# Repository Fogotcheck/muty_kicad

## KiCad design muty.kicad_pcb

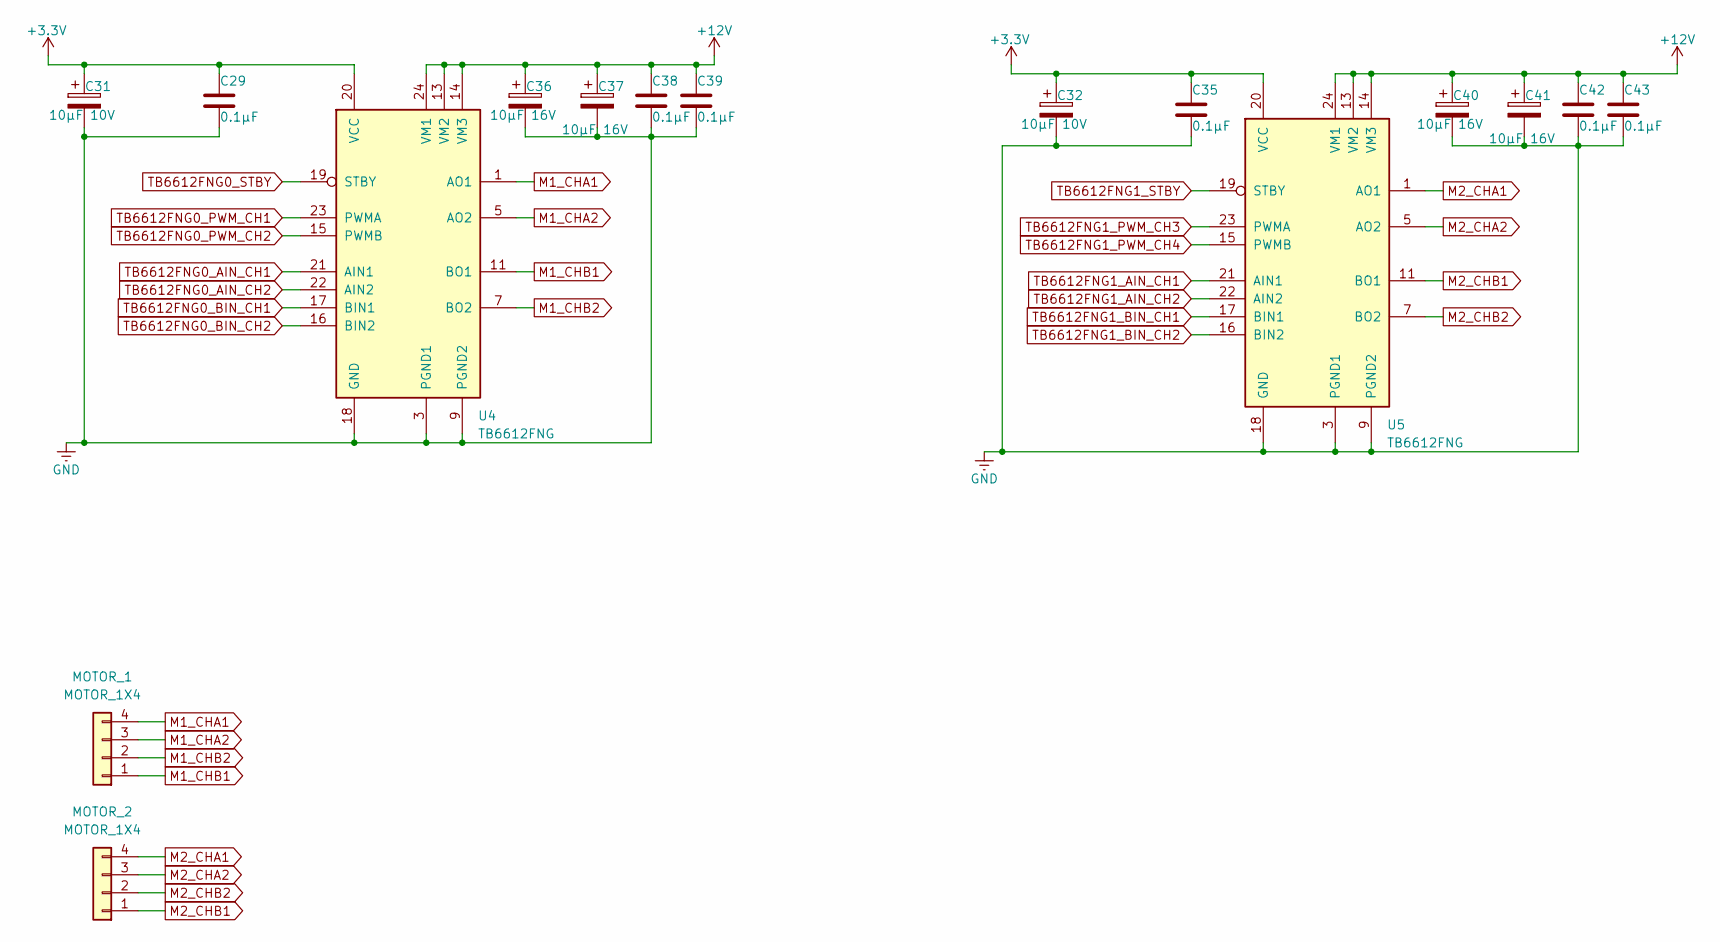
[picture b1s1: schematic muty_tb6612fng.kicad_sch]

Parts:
C29, C35, C38, C39, C42, C43: 0.1μF; C_0603_1608Metric_Pad1.08x0.95mm_HandSolder
C31, C32: 10μF 10V; CP_EIA-1608-10_AVX-L_HandSolder
C36, C37, C40, C41: 10μF 16V; CP_EIA-3528-15_AVX-H_HandSolder
MOTOR_1, MOTOR_2: MOTOR_1X4; JST_EH_S4B-EH_1x04_P2.50mm_Horizontal
U4, U5: TB6612FNG; SSOP-24_5.3x8.2mm_P0.65mm

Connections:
+3.3V: C29.2, C31.1, C32.1, C35.2, U4.20 (VCC), U5.20 (VCC); also elsewhere on the board
+12V: C36.1, C37.1, C38.2, C39.2, C40.1, C41.1, C42.2, C43.2, U4.13 (VM2), U4.14 (VM3), U4.24 (VM1), U5.13 (VM2), U5.14 (VM3), U5.24 (VM1); also elsewhere on the board
GND: C29.1, C31.2, C32.2, C35.1, C36.2, C37.2, C38.1, C39.1, C40.2, C41.2, C42.1, C43.1, U4.3 (PGND1), U4.4 (PGND1), U4.9 (PGND2), U4.10 (PGND2), U4.18 (GND), U5.3 (PGND1), U5.4 (PGND1), U5.9 (PGND2), U5.10 (PGND2), U5.18 (GND); also elsewhere on the board
M1_CHA1: MOTOR_1.4, U4.1 (AO1), U4.2 (AO1)
M1_CHA2: MOTOR_1.3, U4.5 (AO2), U4.6 (AO2)
M1_CHB1: MOTOR_1.1, U4.11 (BO1), U4.12 (BO1)
M1_CHB2: MOTOR_1.2, U4.7 (BO2), U4.8 (BO2)
M2_CHA1: MOTOR_2.4, U5.1 (AO1), U5.2 (AO1)
M2_CHA2: MOTOR_2.3, U5.5 (AO2), U5.6 (AO2)
M2_CHB1: MOTOR_2.1, U5.11 (BO1), U5.12 (BO1)
M2_CHB2: MOTOR_2.2, U5.7 (BO2), U5.8 (BO2)
TB6612FNG0_AIN_CH1: U4.21 (AIN1); also elsewhere on the board
TB6612FNG0_AIN_CH2: U4.22 (AIN2); also elsewhere on the board
TB6612FNG0_BIN_CH1: U4.17 (BIN1); also elsewhere on the board
TB6612FNG0_BIN_CH2: U4.16 (BIN2); also elsewhere on the board
TB6612FNG0_PWM_CH1: U4.23 (PWMA); also elsewhere on the board
TB6612FNG0_PWM_CH2: U4.15 (PWMB); also elsewhere on the board
TB6612FNG0_STBY: U4.19 (STBY); also elsewhere on the board
TB6612FNG1_AIN_CH1: U5.21 (AIN1); also elsewhere on the board
TB6612FNG1_AIN_CH2: U5.22 (AIN2); also elsewhere on the board
TB6612FNG1_BIN_CH1: U5.17 (BIN1); also elsewhere on the board
TB6612FNG1_BIN_CH2: U5.16 (BIN2); also elsewhere on the board
TB6612FNG1_PWM_CH3: U5.23 (PWMA); also elsewhere on the board
TB6612FNG1_PWM_CH4: U5.15 (PWMB); also elsewhere on the board
TB6612FNG1_STBY: U5.19 (STBY); also elsewhere on the board

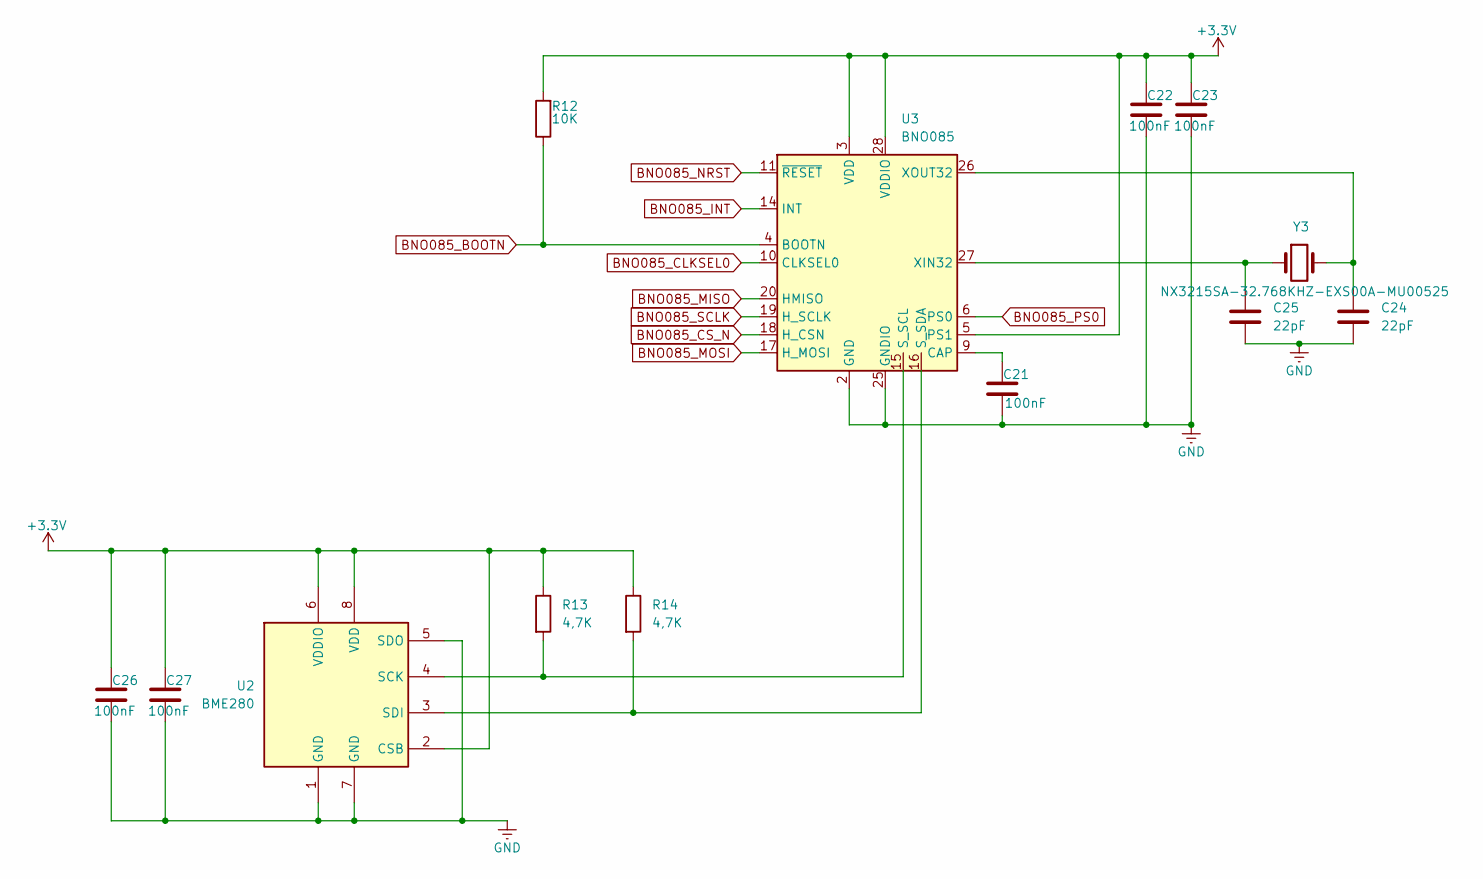
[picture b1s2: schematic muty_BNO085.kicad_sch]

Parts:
C21, C22, C23, C26, C27: 100nF; C_0603_1608Metric_Pad1.08x0.95mm_HandSolder
C24, C25: 22pF; C_0805_2012Metric_Pad1.18x1.45mm_HandSolder
R12: 10K; R_0805_2012Metric_Pad1.20x1.40mm_HandSolder
R13, R14: 4,7K; R_0805_2012Metric_Pad1.20x1.40mm_HandSolder
U2: BME280; Bosch_LGA-8_2.5x2.5mm_P0.65mm_ClockwisePinNumbering
U3: BNO085; LGA-28_5.2x3.8mm_P0.5mm
Y3: NX3215SA-32.768KHZ-EXS00A-MU00525; Crystal_SMD_3215-2Pin_3.2x1.5mm

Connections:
+3.3V: C22.2, C23.2, C26.2, C27.2, R12.2, R13.1, R14.1, U2.2 (CSB), U2.6 (VDDIO), U2.8 (VDD), U3.3 (VDD), U3.5 (PS1), U3.28 (VDDIO); also elsewhere on the board
BNO085_BOOTN: R12.1, U3.4 (BOOTN); also elsewhere on the board
BNO085_CLKSEL0: U3.10 (CLKSEL0); also elsewhere on the board
BNO085_CS_N: U3.18 (H_CSN); also elsewhere on the board
BNO085_INT: U3.14 (INT); also elsewhere on the board
BNO085_MISO: U3.20 (HMISO); also elsewhere on the board
BNO085_MOSI: U3.17 (H_MOSI); also elsewhere on the board
BNO085_NRST: U3.11 (~RESET); also elsewhere on the board
BNO085_PS0: U3.6 (PS0); also elsewhere on the board
BNO085_SCLK: U3.19 (H_SCLK); also elsewhere on the board
GND: C21.1, C22.1, C23.1, C24.1, C25.1, C26.1, C27.1, U2.1 (GND), U2.5 (SDO), U2.7 (GND), U3.2 (GND), U3.25 (GNDIO); also elsewhere on the board
unnamed: R13.2, U2.4 (SCK), U3.15 (S_SCL)
unnamed: R14.2, U2.3 (SDI), U3.16 (S_SDA)
unnamed: C21.2, U3.9 (CAP)
unnamed: C25.2, U3.27 (XIN32), Y3.1
unnamed: C24.2, U3.26 (XOUT32), Y3.2

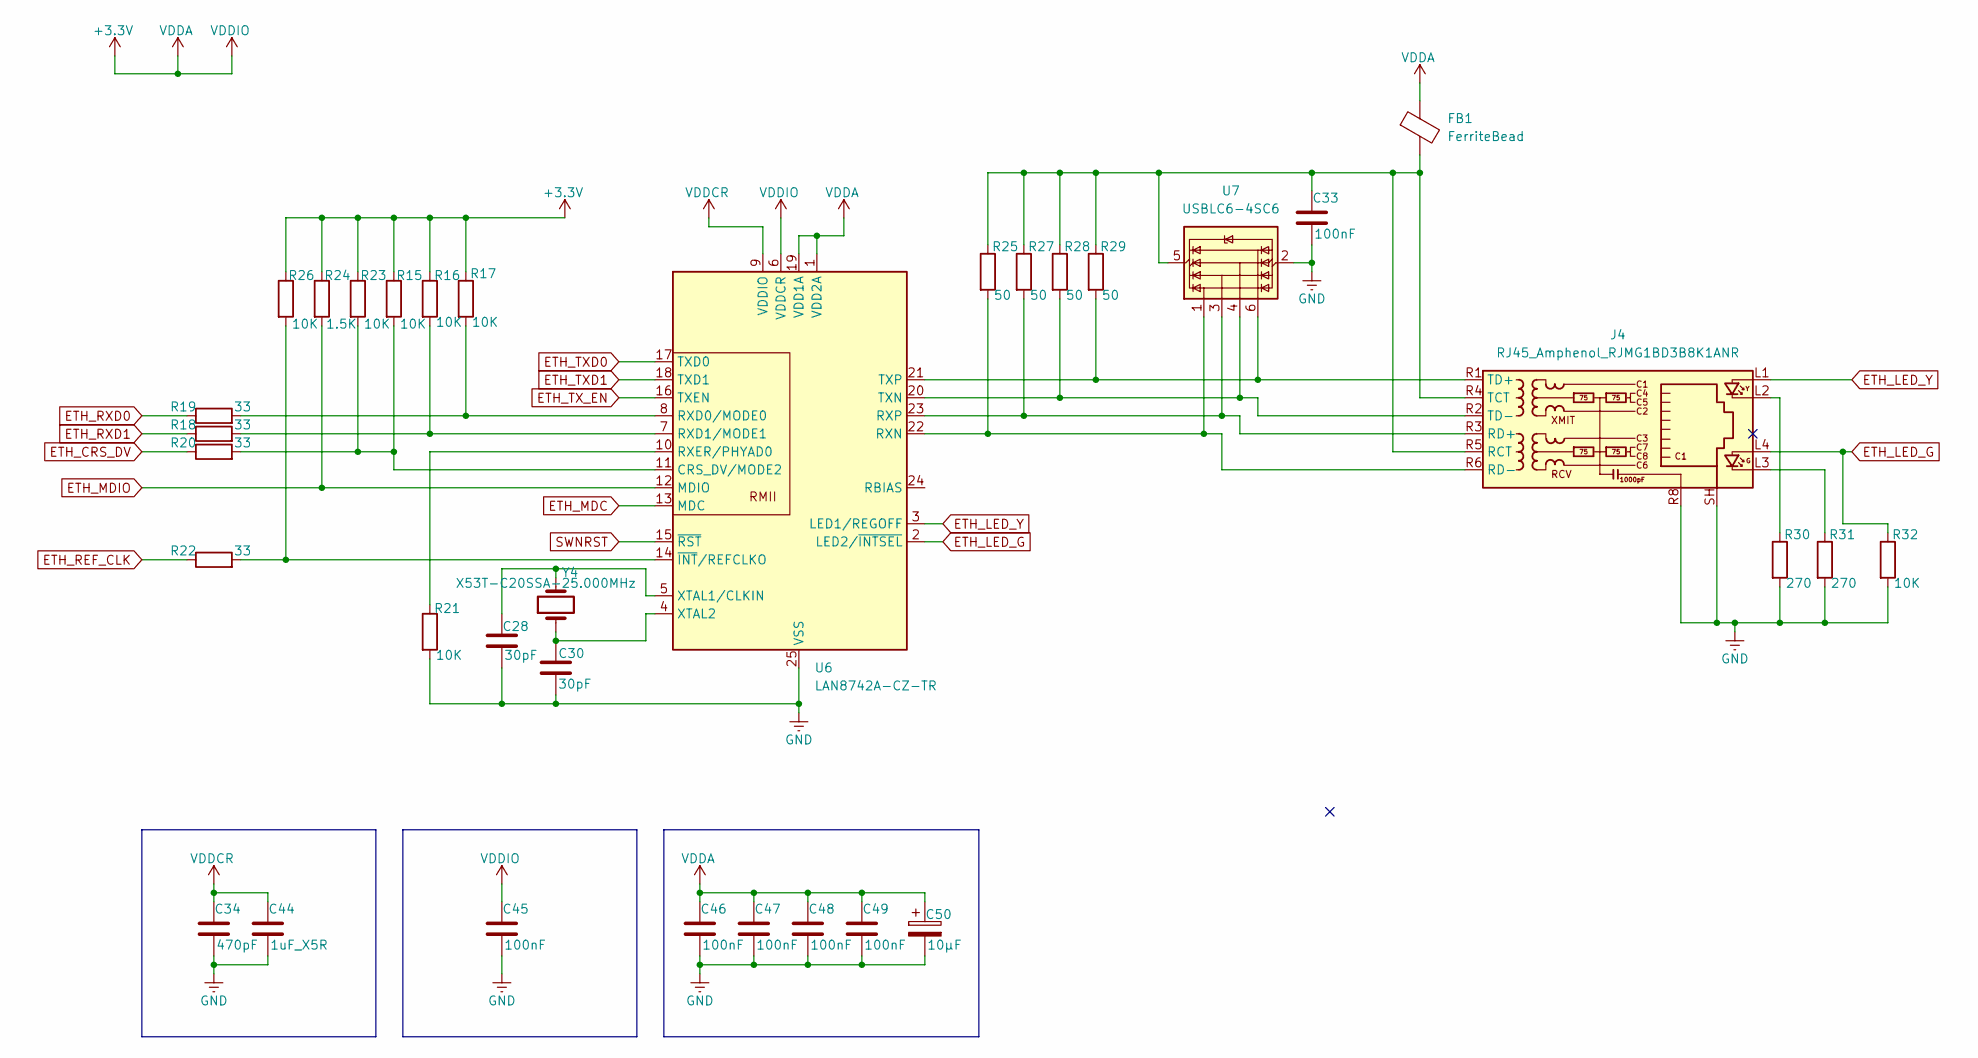
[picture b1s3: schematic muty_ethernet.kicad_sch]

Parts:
C28, C30: 30pF; C_0805_2012Metric_Pad1.18x1.45mm_HandSolder
C33, C45, C46, C47, C48, C49: 100nF; C_0603_1608Metric_Pad1.08x0.95mm_HandSolder
C34: 470pF; C_0603_1608Metric_Pad1.08x0.95mm_HandSolder
C44: 1uF_X5R; C_0603_1608Metric_Pad1.08x0.95mm_HandSolder
C50: 10μF; CP_EIA-1608-10_AVX-L_HandSolder
FB1: FerriteBead; L_0805_2012Metric_Pad1.05x1.20mm_HandSolder
J4: RJ45_Amphenol_RJMG1BD3B8K1ANR
R15, R16, R17, R21, R23, R26, R32: 10K; R_0805_2012Metric_Pad1.20x1.40mm_HandSolder
R18, R19, R20, R22: 33; R_0805_2012Metric_Pad1.20x1.40mm_HandSolder
R24: 1.5K; R_0805_2012Metric_Pad1.20x1.40mm_HandSolder
R25, R27, R28, R29: 50; R_0805_2012Metric_Pad1.20x1.40mm_HandSolder
R30, R31: 270; R_0805_2012Metric_Pad1.20x1.40mm_HandSolder
U6: LAN8742A-CZ-TR; VQFN-24-1EP_4x4mm_P0.5mm_EP2.5x2.5mm_ThermalVias
U7: USBLC6-4SC6; SOT-23-6
Y4: X53T-C20SSA-25.000MHz; Crystal_SMD_5032-2Pin_5.0x3.2mm

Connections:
+3.3V: C45.2, C46.2, C47.2, C48.2, C49.2, C50.1, FB1.1, R15.1, R16.1, R17.1, R23.1, R24.1, R26.1, U6.1 (VDD2A), U6.6 (VDDCR), U6.19 (VDD1A); also elsewhere on the board
ETH_CRS_DV: R20.1; also elsewhere on the board
ETH_LED_G: J4.L4, R32.1, U6.2 (LED2/~INTSEL)
ETH_LED_Y: J4.L1, U6.3 (LED1/REGOFF)
ETH_MDC: U6.13 (MDC); also elsewhere on the board
ETH_MDIO: R24.2, U6.12 (MDIO); also elsewhere on the board
ETH_REF_CLK: R22.1; also elsewhere on the board
ETH_RXD0: R19.1; also elsewhere on the board
ETH_RXD1: R18.1; also elsewhere on the board
ETH_TXD0: U6.17 (TXD0); also elsewhere on the board
ETH_TXD1: U6.18 (TXD1); also elsewhere on the board
ETH_TX_EN: U6.16 (TXEN); also elsewhere on the board
GND: C28.1, C30.1, C33.1, C34.1, C44.1, C45.1, C46.1, C47.1, C48.1, C49.1, C50.2, J4.R8, J4.SH, R21.2, R30.2, R31.2, R32.2, U6.25 (VSS), U7.2 (GND); also elsewhere on the board
unnamed: J4.L2, R30.1
unnamed: J4.L3, R31.1
unnamed: C33.2, FB1.2, J4.R4 (TCT), J4.R5 (RCT), R25.1, R27.1, R28.1, R29.1, U7.5 (VBUS)
unnamed: J4.R3 (RD+), R27.2, U6.23 (RXP), U7.3 (I/O2)
unnamed: J4.R6 (RD-), R25.2, U6.22 (RXN), U7.1 (I/O1)
unnamed: J4.R1 (TD+), R29.2, U6.21 (TXP), U7.6 (I/O4)
unnamed: J4.R2 (TD-), R28.2, U6.20 (TXN), U7.4 (I/O3)
unnamed: R15.2, R20.2, R23.2, U6.11 (CRS_DV/MODE2)
unnamed: R17.2, R19.2, U6.8 (RXD0/MODE0)
unnamed: R16.2, R18.2, U6.7 (RXD1/MODE1)
unnamed: R21.1, U6.10 (RXER/PHYAD0)
unnamed: C28.2, U6.5 (XTAL1/CLKIN), Y4.2
unnamed: C30.2, U6.4 (XTAL2), Y4.1
unnamed: R22.2, R26.2, U6.14 (~INT/REFCLKO)
SWNRST: U6.15 (~RST); also elsewhere on the board
VDDCR: C34.2, C44.2, U6.9 (VDDIO)

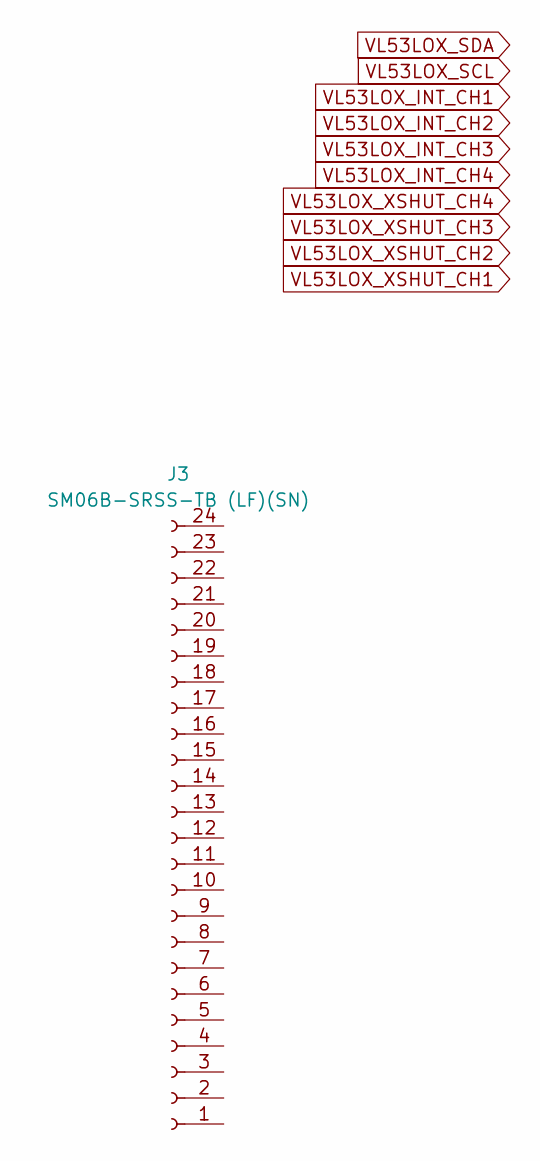
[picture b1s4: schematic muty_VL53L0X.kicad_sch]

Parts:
J3: SM06B-SRSS-TB (LF)(SN)

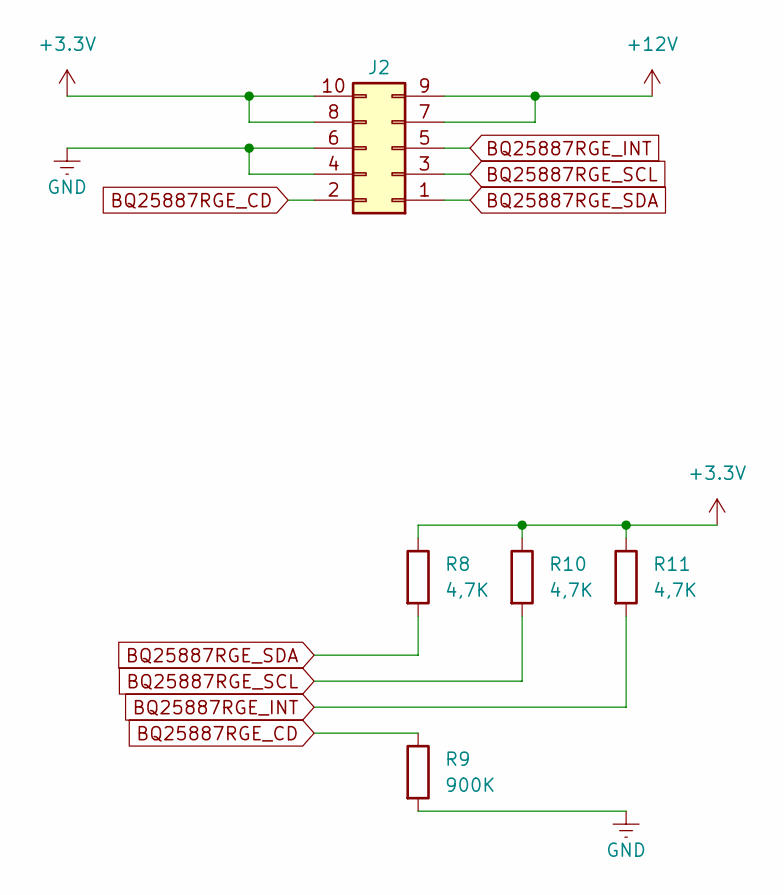
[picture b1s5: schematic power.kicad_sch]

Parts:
J2: Conn_02x05_Odd_Even; JST_PHD_B10B-PHDSS_2x05_P2.00mm_Vertical
R8, R10, R11: 4,7K; R_0805_2012Metric_Pad1.20x1.40mm_HandSolder
R9: 900K; R_0805_2012Metric_Pad1.20x1.40mm_HandSolder

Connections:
+3.3V: J2.8, J2.10, R8.1, R10.1, R11.1; also elsewhere on the board
+12V: J2.7, J2.9; also elsewhere on the board
BQ25887RGE_CD: J2.2, R9.1; also elsewhere on the board
BQ25887RGE_INT: J2.5, R11.2; also elsewhere on the board
BQ25887RGE_SCL: J2.3, R10.2; also elsewhere on the board
BQ25887RGE_SDA: J2.1, R8.2; also elsewhere on the board
GND: J2.4, J2.6, R9.2; also elsewhere on the board

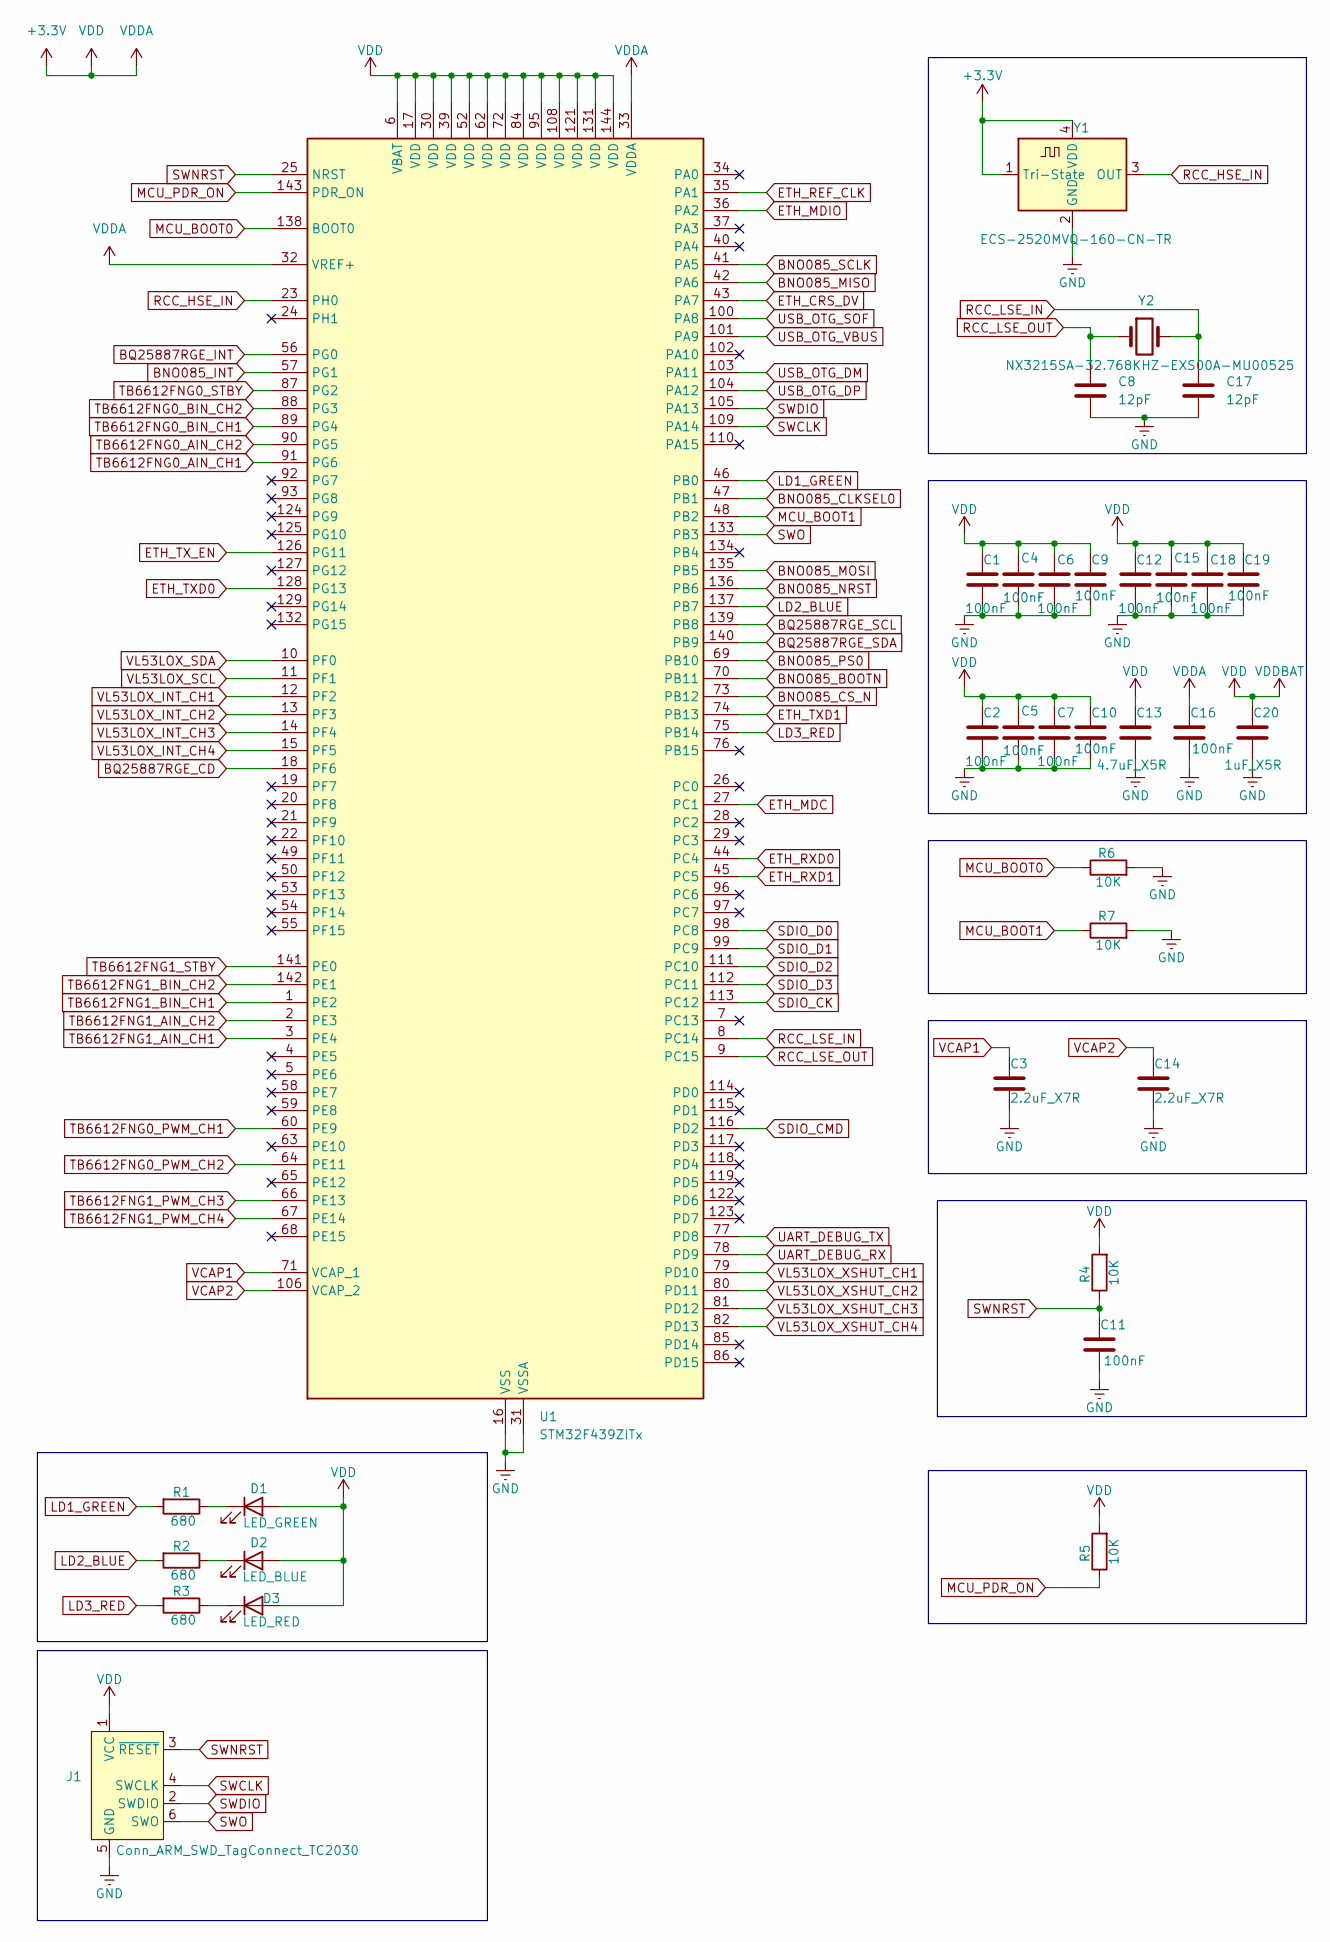
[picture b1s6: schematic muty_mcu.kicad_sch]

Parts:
C1, C2, C4, C5, C6, C7, C9, C10, C11, C12, C15, C16, C18, C19: 100nF; C_0603_1608Metric_Pad1.08x0.95mm_HandSolder
C3, C14: 2.2uF_X7R; C_0805_2012Metric_Pad1.18x1.45mm_HandSolder
C8, C17: 12pF; C_0805_2012Metric_Pad1.18x1.45mm_HandSolder
C13: 4.7uF_X5R; C_0603_1608Metric_Pad1.08x0.95mm_HandSolder
C20: 1uF_X5R; C_0603_1608Metric_Pad1.08x0.95mm_HandSolder
D1: LED_GREEN; LED_0603_1608Metric_Pad1.05x0.95mm_HandSolder
D2: LED_BLUE; LED_0603_1608Metric_Pad1.05x0.95mm_HandSolder
D3: LED_RED; LED_0603_1608Metric_Pad1.05x0.95mm_HandSolder
J1: Conn_ARM_SWD_TagConnect_TC2030; Tag-Connect_TC2030-IDC-FP_2x03_P1.27mm_Vertical
R1, R2, R3: 680; R_0805_2012Metric_Pad1.20x1.40mm_HandSolder
R4, R5, R6, R7: 10K; R_0805_2012Metric_Pad1.20x1.40mm_HandSolder
U1: STM32F439ZITx; LQFP-144_20x20mm_P0.5mm
Y1: ECS-2520MVQ-160-CN-TR; Oscillator_SMD_ECS_2520MV-xxx-xx-4Pin_2.5x2.0mm
Y2: NX3215SA-32.768KHZ-EXS00A-MU00525; Crystal_SMD_3215-2Pin_3.2x1.5mm

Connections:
+3.3V: C1.2, C2.2, C4.2, C5.2, C6.2, C7.2, C9.2, C10.2, C12.2, C13.2, C15.2, C16.2, C18.2, C19.2, C20.2, D1.2 (A), D2.2 (A), D3.2 (A), J1.1 (VCC), R4.2, R5.2, U1.6 (VBAT), U1.17 (VDD), U1.30 (VDD), U1.32 (VREF+), U1.33 (VDDA), U1.39 (VDD), U1.52 (VDD), U1.62 (VDD), U1.72 (VDD), U1.84 (VDD), U1.95 (VDD), U1.108 (VDD), U1.121 (VDD), U1.131 (VDD), U1.144 (VDD), Y1.1 (Tri-State), Y1.4 (VDD); also elsewhere on the board
BNO085_BOOTN: U1.70 (PB11); also elsewhere on the board
BNO085_CLKSEL0: U1.47 (PB1); also elsewhere on the board
BNO085_CS_N: U1.73 (PB12); also elsewhere on the board
BNO085_INT: U1.57 (PG1); also elsewhere on the board
BNO085_MISO: U1.42 (PA6); also elsewhere on the board
BNO085_MOSI: U1.135 (PB5); also elsewhere on the board
BNO085_NRST: U1.136 (PB6); also elsewhere on the board
BNO085_PS0: U1.69 (PB10); also elsewhere on the board
BNO085_SCLK: U1.41 (PA5); also elsewhere on the board
BQ25887RGE_CD: U1.18 (PF6); also elsewhere on the board
BQ25887RGE_INT: U1.56 (PG0); also elsewhere on the board
BQ25887RGE_SCL: U1.139 (PB8); also elsewhere on the board
BQ25887RGE_SDA: U1.140 (PB9); also elsewhere on the board
ETH_CRS_DV: U1.43 (PA7); also elsewhere on the board
ETH_MDC: U1.27 (PC1); also elsewhere on the board
ETH_MDIO: U1.36 (PA2); also elsewhere on the board
ETH_REF_CLK: U1.35 (PA1); also elsewhere on the board
ETH_RXD0: U1.44 (PC4); also elsewhere on the board
ETH_RXD1: U1.45 (PC5); also elsewhere on the board
ETH_TXD0: U1.128 (PG13); also elsewhere on the board
ETH_TXD1: U1.74 (PB13); also elsewhere on the board
ETH_TX_EN: U1.126 (PG11); also elsewhere on the board
GND: C1.1, C2.1, C3.1, C4.1, C5.1, C6.1, C7.1, C8.1, C9.1, C10.1, C11.1, C12.1, C13.1, C14.1, C15.1, C16.1, C17.1, C18.1, C19.1, C20.1, J1.5 (GND), R6.2, R7.2, U1.16 (VSS), U1.31 (VSSA), U1.38 (VSS), U1.51 (VSS), U1.61 (VSS), U1.83 (VSS), U1.94 (VSS), U1.107 (VSS), U1.120 (VSS), U1.130 (VSS), Y1.2 (GND); also elsewhere on the board
LD1_GREEN: R1.2, U1.46 (PB0)
LD2_BLUE: R2.2, U1.137 (PB7)
LD3_RED: R3.2, U1.75 (PB14)
MCU_BOOT0: R6.1, U1.138 (BOOT0)
MCU_BOOT1: R7.1, U1.48 (PB2)
MCU_PDR_ON: R5.1, U1.143 (PDR_ON)
unnamed: D1.1 (K), R1.1
unnamed: D2.1 (K), R2.1
unnamed: D3.1 (K), R3.1
RCC_HSE_IN: U1.23 (PH0), Y1.3 (OUT)
RCC_LSE_IN: C17.2, U1.8 (PC14), Y2.2
RCC_LSE_OUT: C8.2, U1.9 (PC15), Y2.1
SDIO_CK: U1.113 (PC12)
SDIO_CMD: U1.116 (PD2)
SDIO_D0: U1.98 (PC8)
SDIO_D1: U1.99 (PC9)
SDIO_D2: U1.111 (PC10)
SDIO_D3: U1.112 (PC11)
SWCLK: J1.4 (SWCLK), U1.109 (PA14)
SWDIO: J1.2 (SWDIO), U1.105 (PA13)
SWNRST: C11.2, J1.3 (~RESET), R4.1, U1.25 (NRST); also elsewhere on the board
SWO: J1.6 (SWO), U1.133 (PB3)
TB6612FNG0_AIN_CH1: U1.91 (PG6); also elsewhere on the board
TB6612FNG0_AIN_CH2: U1.90 (PG5); also elsewhere on the board
TB6612FNG0_BIN_CH1: U1.89 (PG4); also elsewhere on the board
TB6612FNG0_BIN_CH2: U1.88 (PG3); also elsewhere on the board
TB6612FNG0_PWM_CH1: U1.60 (PE9); also elsewhere on the board
TB6612FNG0_PWM_CH2: U1.64 (PE11); also elsewhere on the board
TB6612FNG0_STBY: U1.87 (PG2); also elsewhere on the board
TB6612FNG1_AIN_CH1: U1.3 (PE4); also elsewhere on the board
TB6612FNG1_AIN_CH2: U1.2 (PE3); also elsewhere on the board
TB6612FNG1_BIN_CH1: U1.1 (PE2); also elsewhere on the board
TB6612FNG1_BIN_CH2: U1.142 (PE1); also elsewhere on the board
TB6612FNG1_PWM_CH3: U1.66 (PE13); also elsewhere on the board
TB6612FNG1_PWM_CH4: U1.67 (PE14); also elsewhere on the board
TB6612FNG1_STBY: U1.141 (PE0); also elsewhere on the board
UART_DEBUG_RX: U1.78 (PD9)
UART_DEBUG_TX: U1.77 (PD8)
USB_OTG_DM: U1.103 (PA11)
USB_OTG_DP: U1.104 (PA12)
USB_OTG_SOF: U1.100 (PA8)
USB_OTG_VBUS: U1.101 (PA9)
VCAP1: C3.2, U1.71 (VCAP_1)
VCAP2: C14.2, U1.106 (VCAP_2)
VL53LOX_INT_CH1: U1.12 (PF2)
VL53LOX_INT_CH2: U1.13 (PF3)
VL53LOX_INT_CH3: U1.14 (PF4)
VL53LOX_INT_CH4: U1.15 (PF5)
VL53LOX_SCL: U1.11 (PF1)
VL53LOX_SDA: U1.10 (PF0)
VL53LOX_XSHUT_CH1: U1.79 (PD10)
VL53LOX_XSHUT_CH2: U1.80 (PD11)
VL53LOX_XSHUT_CH3: U1.81 (PD12)
VL53LOX_XSHUT_CH4: U1.82 (PD13)

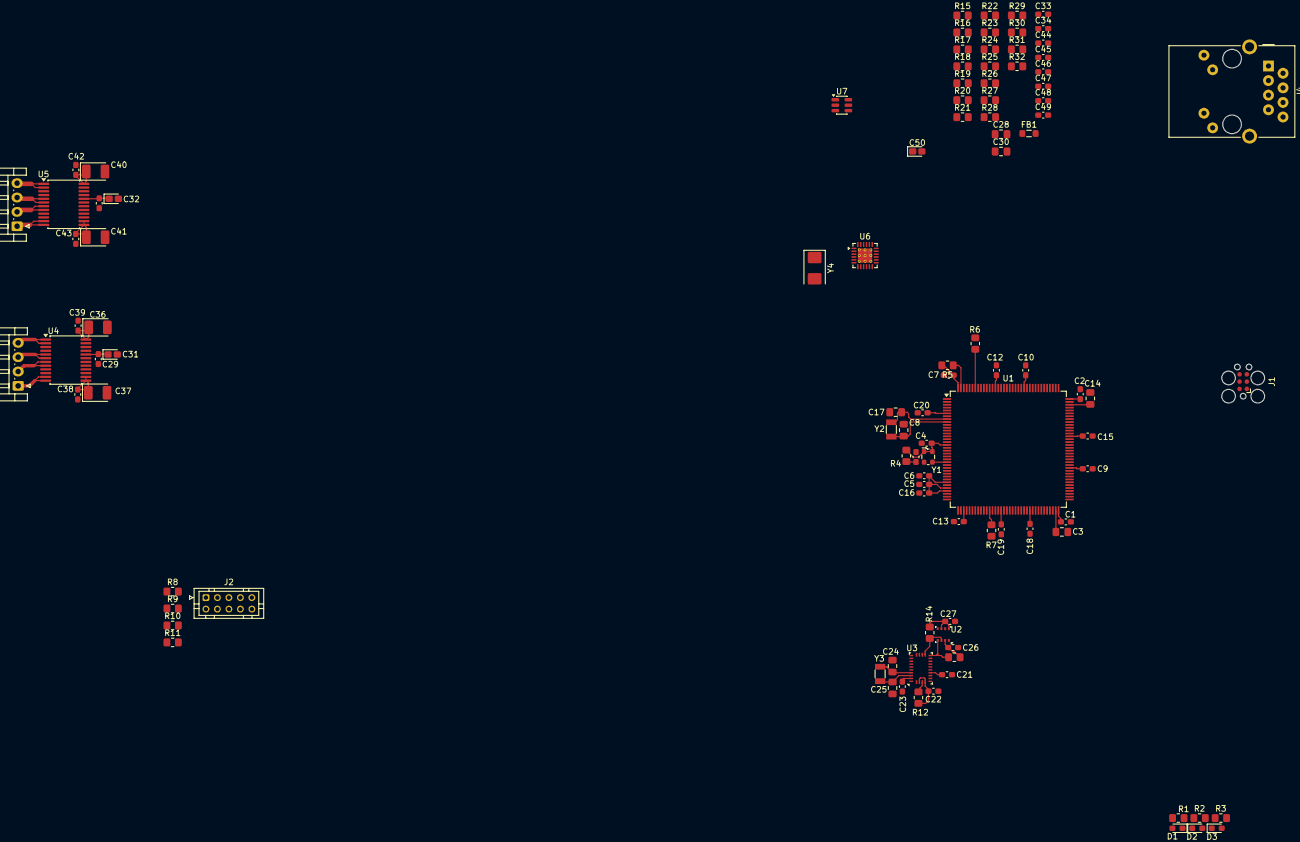
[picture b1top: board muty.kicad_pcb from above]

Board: 4 copper layers, 102 parts (0 on the bottom side), 87 nets.

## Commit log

2025-11-20 Initial
2025-11-21 feat: add bq25887 connector
2025-11-21 feat: add bno085+bme280
2025-11-21 feat: add tb6612fng
2025-11-22 feat: add ethernet
